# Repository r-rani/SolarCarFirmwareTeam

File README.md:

# SolarCarFirmwareTeam
Firmware and CANBUS implementation across the Solar Car

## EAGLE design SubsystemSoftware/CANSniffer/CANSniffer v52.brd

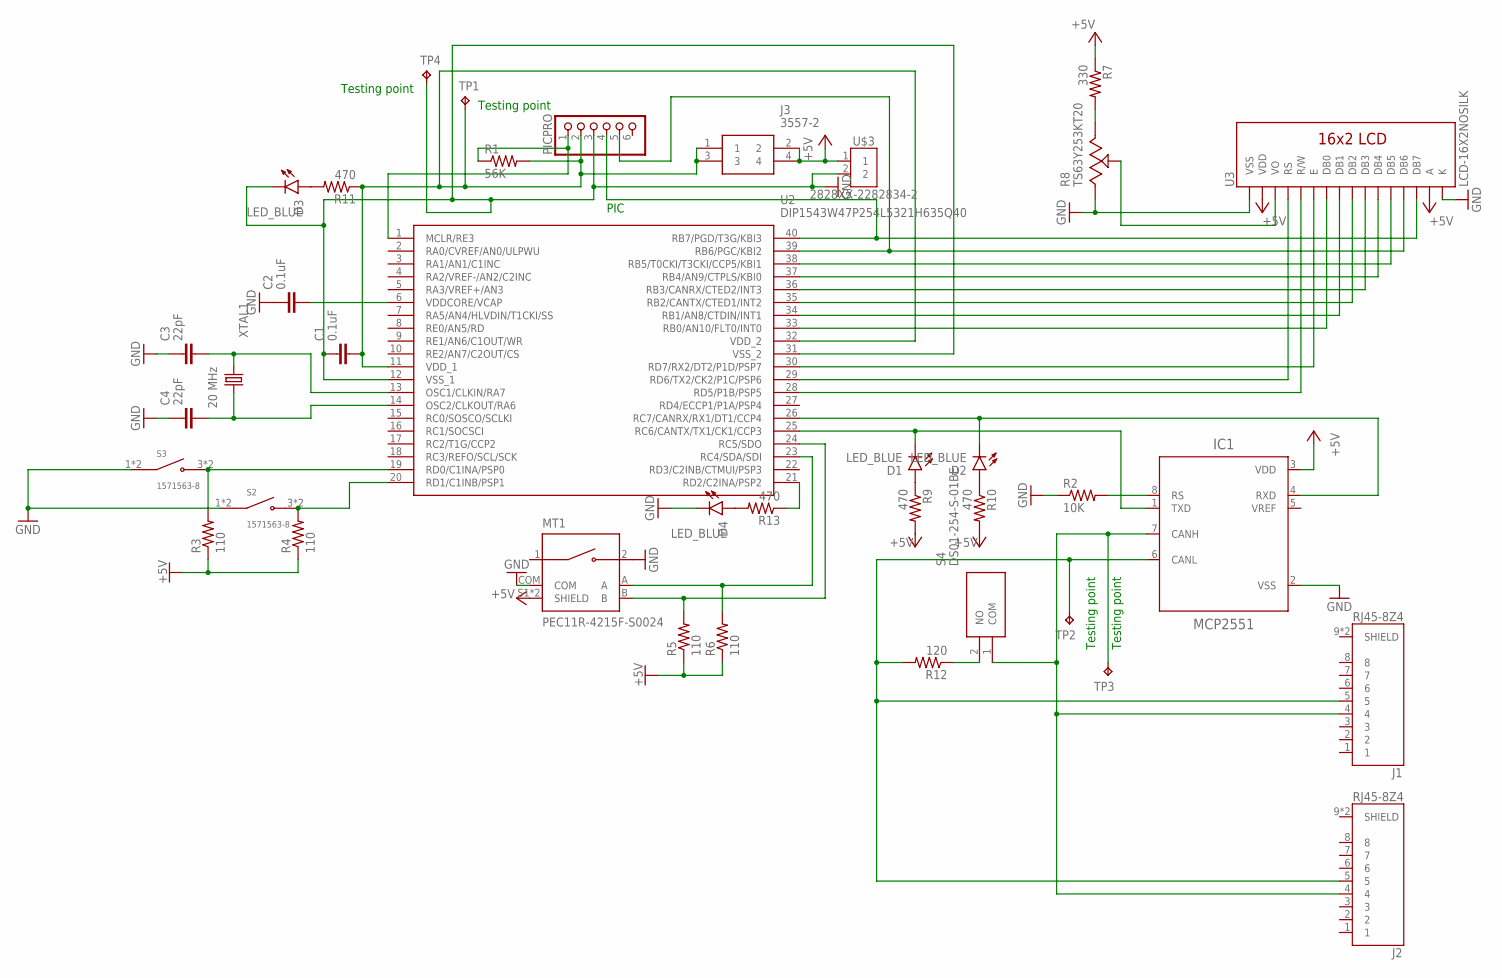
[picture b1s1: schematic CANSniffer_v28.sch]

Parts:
C1, C2: 0.1uF; CAPC3216X135
C3, C4: 22pF; CAPC3216X135
D1, D2, D3, D4: LED_BLUE; LEDC1005X25N_FLAT-B
IC1: MCP2551; DIP1092W55P254L949H533Q8B
J1, J2: RJ45-8Z4; TE_RJ45-8Z4
J3: 3557-2
MT1: PEC11R-4215F-S0024; XDCR_PEC11R-4215F-S0024
PICPRO: PINHD-1X6; 1X06
R1: 56K; R0603
R2: 10K; R0603
R3, R4, R5, R6: 110; R0603
R7: 330; R0603
R8: TS63Y253KT20; TRIM_TS63Y253KT20
R9, R10, R11, R13: 470; R0603
R12: 120; R0603
S2, S3: 1571563-8; SW_1571563-8
S4: DS01-254-S-01BE; DS01254S01BE
TP1, TP2, TP3, TP4: TPTP16R; TP16R
U2: DIP1543W47P254L5321H635Q40
U3: LCD-16X2NOSILK; LCD-16X2_NOSILK
U$3: 2828XX-2282834-2; TERMBLK_254-2N
XTAL1: 20 MHz; XTALRR488W45L1150T500H350B

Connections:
+5V: IC1.3 (VDD), J3.2, J3.4, MT1.S1 (SHIELD), MT1.S2 (SHIELD), R3.1, R4.1, R5.1, R6.1, R7.1, R9.2, R10.2, U3.2 (VDD), U3.15 (A), U$3.1
GND: C1.1, C2.1, C3.1, C4.1, D3.C, D4.C, IC1.2 (VSS), MT1.2, MT1.COM, PICPRO.3, R2.1, S2.1 (COM), S2.2 (COM), S3.1 (COM), S3.2 (COM), TP4.TP, U2.12 (VSS_1), U2.31 (VSS_2), U3.16 (K), U$3.2
unnamed: PICPRO.1, R1.1, U2.1 (MCLR/RE3)
unnamed: U2.33 (RB0/AN10/FLT0/INT0), U3.7 (DB0)
unnamed: IC1.8 (RS), R2.2
unnamed: D1.C, IC1.1 (TXD), U2.25 (RC6/CANTX/TX1/CK1/CCP3)
unnamed: PICPRO.4, U2.40 (RB7/PGD/T3G/KBI3), U3.14 (DB7)
unnamed: PICPRO.5, U2.39 (RB6/PGC/KBI2), U3.13 (DB6)
unnamed: U2.34 (RB1/AN8/CTDIN/INT1), U3.8 (DB1)
unnamed: U2.35 (RB2/CANTX/CTED1/INT2), U3.9 (DB2)
unnamed: D2.C, IC1.4 (RXD), U2.26 (RC7/CANRX/RX1/DT1/CCP4)
unnamed: C3.2, U2.13 (OSC1/CLKIN/RA7), XTAL1.1
unnamed: C4.2, U2.14 (OSC2/CLKOUT/RA6), XTAL1.2
unnamed: IC1.6 (CANL), J1.5, J2.5, R12.2, TP2.TP
unnamed: IC1.7 (CANH), J1.4, J2.4, S4.1 (COM), TP3.TP
unnamed: U2.36 (RB3/CANRX/CTED2/INT3), U3.10 (DB3)
unnamed: U2.37 (RB4/AN9/CTPLS/KBI0), U3.11 (DB4)
unnamed: U2.38 (RB5/T0CKI/T3CKI/CCP5/KBI1), U3.12 (DB5)
unnamed: U2.28 (RD5/P1B/PSP5), U3.5 (R/W)
unnamed: U2.29 (RD6/TX2/CK2/P1C/PSP6), U3.4 (RS)
unnamed: U2.30 (RD7/RX2/DT2/P1D/PSP7), U3.6 (E)
unnamed: D2.A, R10.1
unnamed: R7.2, R8.3 (C)
unnamed: R3.2, S3.3 (NO), S3.4 (NO), U2.19 (RD0/C1INA/PSP0)
unnamed: R4.2, S2.3 (NO), S2.4 (NO), U2.20 (RD1/C1INB/PSP1)
unnamed: C2.2, U2.6 (VDDCORE/VCAP)
unnamed: MT1.A, R6.2, U2.23 (RC4/SDA/SDI)
unnamed: MT1.B, R5.2, U2.24 (RC5/SDO)
unnamed: R8.2 (B), U3.3 (VO)
unnamed: D1.A, R9.1
unnamed: R12.1, S4.2 (NO)
unnamed: C1.2, J3.1, J3.3, PICPRO.2, R1.2, R11.1, TP1.TP, U2.11 (VDD_1), U2.32 (VDD_2)
unnamed: R8.1 (A), U3.1 (VSS)
unnamed: D3.A, R11.2
unnamed: D4.A, R13.2
unnamed: R13.1, U2.21 (RD2/C2INA/PSP2)

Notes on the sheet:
PIC
Testing point

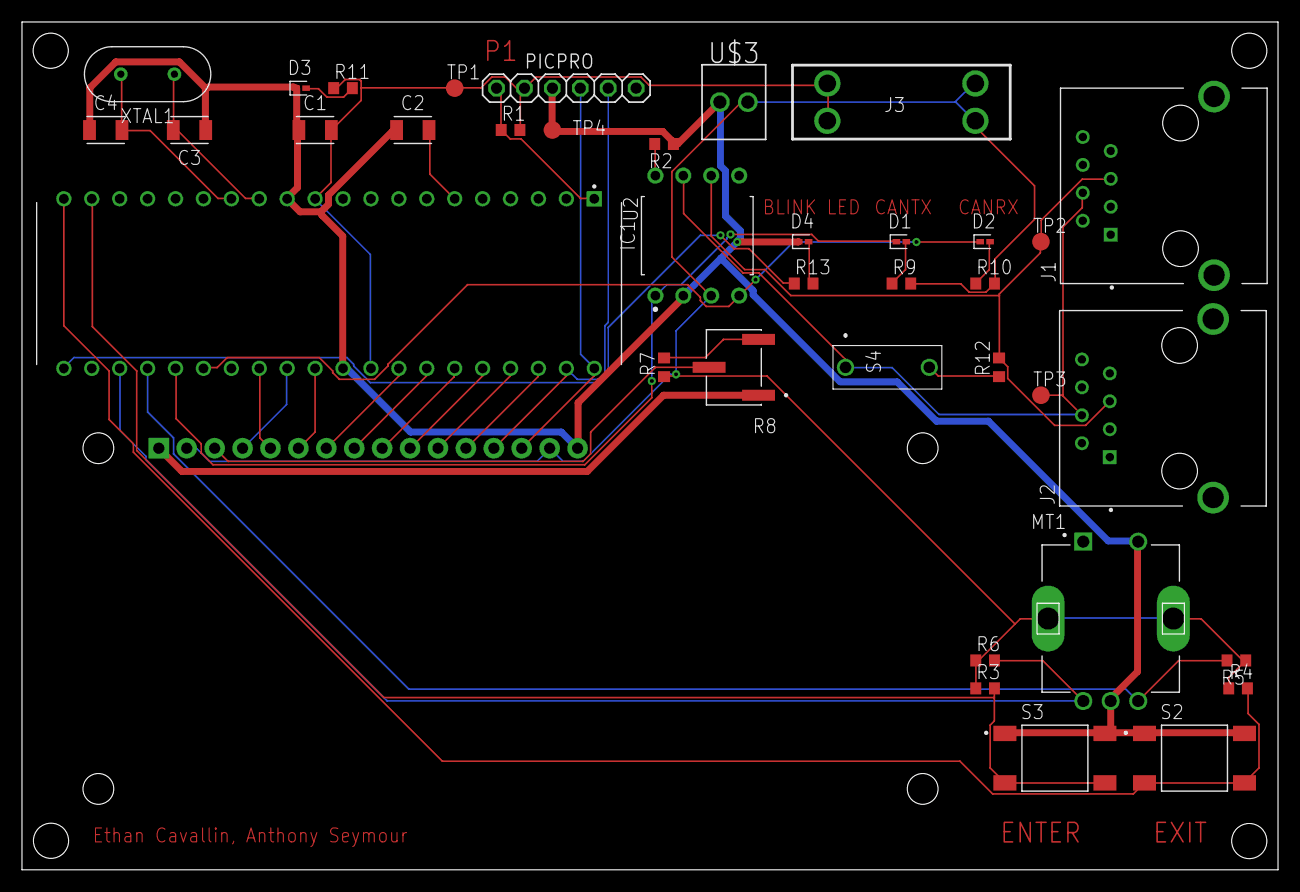
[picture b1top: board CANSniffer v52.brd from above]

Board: 2 copper layers, 114.3 x 77.1 mm, 38 parts (0 on the bottom side), 36 nets.

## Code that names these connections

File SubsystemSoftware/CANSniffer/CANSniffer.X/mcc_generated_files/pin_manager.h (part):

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// get/set IO_RB0 aliases
#define IO_RB0_TRIS                 TRISBbits.TRISB0
#define IO_RB0_LAT                  LATBbits.LATB0
#define IO_RB0_PORT                 PORTBbits.RB0
#define IO_RB0_WPU                  WPUBbits.WPUB0
#define IO_RB0_ANS                  ANCON1bits.ANSEL10
#define IO_RB0_SetHigh()            do { LATBbits.LATB0 = 1; } while(0)
#define IO_RB0_SetLow()             do { LATBbits.LATB0 = 0; } while(0)
#define IO_RB0_Toggle()             do { LATBbits.LATB0 = ~LATBbits.LATB0; } while(0)
#define IO_RB0_GetValue()           PORTBbits.RB0
#define IO_RB0_SetDigitalInput()    do { TRISBbits.TRISB0 = 1; } while(0)
#define IO_RB0_SetDigitalOutput()   do { TRISBbits.TRISB0 = 0; } while(0)
#define IO_RB0_SetPullup()          do { WPUBbits.WPUB0 = 1; } while(0)
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// get/set IO_RB1 aliases
#define IO_RB1_TRIS                 TRISBbits.TRISB1
#define IO_RB1_LAT                  LATBbits.LATB1
#define IO_RB1_PORT                 PORTBbits.RB1
#define IO_RB1_WPU                  WPUBbits.WPUB1
#define IO_RB1_ANS                  ANCON1bits.ANSEL8
#define IO_RB1_SetHigh()            do { LATBbits.LATB1 = 1; } while(0)
#define IO_RB1_SetLow()             do { LATBbits.LATB1 = 0; } while(0)
#define IO_RB1_Toggle()             do { LATBbits.LATB1 = ~LATBbits.LATB1; } while(0)
#define IO_RB1_GetValue()           PORTBbits.RB1
#define IO_RB1_SetDigitalInput()    do { TRISBbits.TRISB1 = 1; } while(0)
#define IO_RB1_SetDigitalOutput()   do { TRISBbits.TRISB1 = 0; } while(0)
#define IO_RB1_SetPullup()          do { WPUBbits.WPUB1 = 1; } while(0)
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// get/set IO_RB2 aliases
#define IO_RB2_TRIS                 TRISBbits.TRISB2
#define IO_RB2_LAT                  LATBbits.LATB2
#define IO_RB2_PORT                 PORTBbits.RB2
#define IO_RB2_WPU                  WPUBbits.WPUB2
#define IO_RB2_SetHigh()            do { LATBbits.LATB2 = 1; } while(0)
#define IO_RB2_SetLow()             do { LATBbits.LATB2 = 0; } while(0)
#define IO_RB2_Toggle()             do { LATBbits.LATB2 = ~LATBbits.LATB2; } while(0)
#define IO_RB2_GetValue()           PORTBbits.RB2
#define IO_RB2_SetDigitalInput()    do { TRISBbits.TRISB2 = 1; } while(0)
#define IO_RB2_SetDigitalOutput()   do { TRISBbits.TRISB2 = 0; } while(0)
#define IO_RB2_SetPullup()          do { WPUBbits.WPUB2 = 1; } while(0)
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// get/set IO_RB3 aliases
#define IO_RB3_TRIS                 TRISBbits.TRISB3
#define IO_RB3_LAT                  LATBbits.LATB3
#define IO_RB3_PORT                 PORTBbits.RB3
#define IO_RB3_WPU                  WPUBbits.WPUB3
#define IO_RB3_SetHigh()            do { LATBbits.LATB3 = 1; } while(0)
#define IO_RB3_SetLow()             do { LATBbits.LATB3 = 0; } while(0)
#define IO_RB3_Toggle()             do { LATBbits.LATB3 = ~LATBbits.LATB3; } while(0)
#define IO_RB3_GetValue()           PORTBbits.RB3
#define IO_RB3_SetDigitalInput()    do { TRISBbits.TRISB3 = 1; } while(0)
#define IO_RB3_SetDigitalOutput()   do { TRISBbits.TRISB3 = 0; } while(0)
#define IO_RB3_SetPullup()          do { WPUBbits.WPUB3 = 1; } while(0)
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// get/set IO_RB4 aliases
#define IO_RB4_TRIS                 TRISBbits.TRISB4
#define IO_RB4_LAT                  LATBbits.LATB4
#define IO_RB4_PORT                 PORTBbits.RB4
#define IO_RB4_WPU                  WPUBbits.WPUB4
#define IO_RB4_ANS                  ANCON1bits.ANSEL9
#define IO_RB4_SetHigh()            do { LATBbits.LATB4 = 1; } while(0)
#define IO_RB4_SetLow()             do { LATBbits.LATB4 = 0; } while(0)
#define IO_RB4_Toggle()             do { LATBbits.LATB4 = ~LATBbits.LATB4; } while(0)
#define IO_RB4_GetValue()           PORTBbits.RB4
#define IO_RB4_SetDigitalInput()    do { TRISBbits.TRISB4 = 1; } while(0)
#define IO_RB4_SetDigitalOutput()   do { TRISBbits.TRISB4 = 0; } while(0)
#define IO_RB4_SetPullup()          do { WPUBbits.WPUB4 = 1; } while(0)
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// get/set IO_RB5 aliases
#define IO_RB5_TRIS                 TRISBbits.TRISB5
#define IO_RB5_LAT                  LATBbits.LATB5
#define IO_RB5_PORT                 PORTBbits.RB5
#define IO_RB5_WPU                  WPUBbits.WPUB5
#define IO_RB5_SetHigh()            do { LATBbits.LATB5 = 1; } while(0)
#define IO_RB5_SetLow()             do { LATBbits.LATB5 = 0; } while(0)
#define IO_RB5_Toggle()             do { LATBbits.LATB5 = ~LATBbits.LATB5; } while(0)
#define IO_RB5_GetValue()           PORTBbits.RB5
#define IO_RB5_SetDigitalInput()    do { TRISBbits.TRISB5 = 1; } while(0)
#define IO_RB5_SetDigitalOutput()   do { TRISBbits.TRISB5 = 0; } while(0)
#define IO_RB5_SetPullup()          do { WPUBbits.WPUB5 = 1; } while(0)
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// get/set IO_RB6 aliases
#define IO_RB6_TRIS                 TRISBbits.TRISB6
#define IO_RB6_LAT                  LATBbits.LATB6
#define IO_RB6_PORT                 PORTBbits.RB6
#define IO_RB6_WPU                  WPUBbits.WPUB6
#define IO_RB6_SetHigh()            do { LATBbits.LATB6 = 1; } while(0)
#define IO_RB6_SetLow()             do { LATBbits.LATB6 = 0; } while(0)
#define IO_RB6_Toggle()             do { LATBbits.LATB6 = ~LATBbits.LATB6; } while(0)
#define IO_RB6_GetValue()           PORTBbits.RB6
#define IO_RB6_SetDigitalInput()    do { TRISBbits.TRISB6 = 1; } while(0)
#define IO_RB6_SetDigitalOutput()   do { TRISBbits.TRISB6 = 0; } while(0)
#define IO_RB6_SetPullup()          do { WPUBbits.WPUB6 = 1; } while(0)
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// get/set IO_RB7 aliases
#define IO_RB7_TRIS                 TRISBbits.TRISB7
#define IO_RB7_LAT                  LATBbits.LATB7
#define IO_RB7_PORT                 PORTBbits.RB7
#define IO_RB7_WPU                  WPUBbits.WPUB7
#define IO_RB7_SetHigh()            do { LATBbits.LATB7 = 1; } while(0)
#define IO_RB7_SetLow()             do { LATBbits.LATB7 = 0; } while(0)
#define IO_RB7_Toggle()             do { LATBbits.LATB7 = ~LATBbits.LATB7; } while(0)
#define IO_RB7_GetValue()           PORTBbits.RB7
#define IO_RB7_SetDigitalInput()    do { TRISBbits.TRISB7 = 1; } while(0)
#define IO_RB7_SetDigitalOutput()   do { TRISBbits.TRISB7 = 0; } while(0)
#define IO_RB7_SetPullup()          do { WPUBbits.WPUB7 = 1; } while(0)
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// get/set IO_RC4 aliases
#define IO_RC4_TRIS                 TRISCbits.TRISC4
#define IO_RC4_LAT                  LATCbits.LATC4
#define IO_RC4_PORT                 PORTCbits.RC4
#define IO_RC4_SetHigh()            do { LATCbits.LATC4 = 1; } while(0)
#define IO_RC4_SetLow()             do { LATCbits.LATC4 = 0; } while(0)
#define IO_RC4_Toggle()             do { LATCbits.LATC4 = ~LATCbits.LATC4; } while(0)
#define IO_RC4_GetValue()           PORTCbits.RC4
#define IO_RC4_SetDigitalInput()    do { TRISCbits.TRISC4 = 1; } while(0)
#define IO_RC4_SetDigitalOutput()   do { TRISCbits.TRISC4 = 0; } while(0)

// get/set IO_RC5 aliases
#define IO_RC5_TRIS                 TRISCbits.TRISC5
#define IO_RC5_LAT                  LATCbits.LATC5
#define IO_RC5_PORT                 PORTCbits.RC5
#define IO_RC5_SetHigh()            do { LATCbits.LATC5 = 1; } while(0)
#define IO_RC5_SetLow()             do { LATCbits.LATC5 = 0; } while(0)
#define IO_RC5_Toggle()             do { LATCbits.LATC5 = ~LATCbits.LATC5; } while(0)
#define IO_RC5_GetValue()           PORTCbits.RC5
#define IO_RC5_SetDigitalInput()    do { TRISCbits.TRISC5 = 1; } while(0)
#define IO_RC5_SetDigitalOutput()   do { TRISCbits.TRISC5 = 0; } while(0)

// get/set IO_RC6 aliases
#define IO_RC6_TRIS                 TRISCbits.TRISC6
#define IO_RC6_LAT                  LATCbits.LATC6
#define IO_RC6_PORT                 PORTCbits.RC6
#define IO_RC6_SetHigh()            do { LATCbits.LATC6 = 1; } while(0)
#define IO_RC6_SetLow()             do { LATCbits.LATC6 = 0; } while(0)
#define IO_RC6_Toggle()             do { LATCbits.LATC6 = ~LATCbits.LATC6; } while(0)
#define IO_RC6_GetValue()           PORTCbits.RC6
#define IO_RC6_SetDigitalInput()    do { TRISCbits.TRISC6 = 1; } while(0)
#define IO_RC6_SetDigitalOutput()   do { TRISCbits.TRISC6 = 0; } while(0)

// get/set IO_RC7 aliases
#define IO_RC7_TRIS                 TRISCbits.TRISC7
#define IO_RC7_LAT                  LATCbits.LATC7
#define IO_RC7_PORT                 PORTCbits.RC7
#define IO_RC7_SetHigh()            do { LATCbits.LATC7 = 1; } while(0)
#define IO_RC7_SetLow()             do { LATCbits.LATC7 = 0; } while(0)
#define IO_RC7_Toggle()             do { LATCbits.LATC7 = ~LATCbits.LATC7; } while(0)
#define IO_RC7_GetValue()           PORTCbits.RC7
#define IO_RC7_SetDigitalInput()    do { TRISCbits.TRISC7 = 1; } while(0)
#define IO_RC7_SetDigitalOutput()   do { TRISCbits.TRISC7 = 0; } while(0)

// get/set IO_RD0 aliases
#define IO_RD0_TRIS                 TRISDbits.TRISD0
#define IO_RD0_LAT                  LATDbits.LATD0
#define IO_RD0_PORT                 PORTDbits.RD0
#define IO_RD0_ANS                  ANCON1bits.ANSEL11
#define IO_RD0_SetHigh()            do { LATDbits.LATD0 = 1; } while(0)
#define IO_RD0_SetLow()             do { LATDbits.LATD0 = 0; } while(0)
#define IO_RD0_Toggle()             do { LATDbits.LATD0 = ~LATDbits.LATD0; } while(0)
#define IO_RD0_GetValue()           PORTDbits.RD0
#define IO_RD0_SetDigitalInput()    do { TRISDbits.TRISD0 = 1; } while(0)
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
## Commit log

2023-03-04 Code for LV
2023-03-04 changed folder name
2023-03-04 BMS Datasheet
2023-03-05 Added DDISP
2023-03-05 Added CANSniffer
2023-03-05 Uploaded CANSniffer Schematics
2023-03-12 test commit to master
2023-03-12 Added functionality to LCD
2023-03-26 Made changes to DDISP firmware
2023-04-02 Motor Controller Can IDs Header File
2023-05-13 added canbus test code
2023-07-09 PMS Updated Code Rev1
2023-07-17 PMS Updated Code - Compilation Working
2023-07-17 PMS Updated Code - Building Successfully (ignore previous commit pls)
2023-07-20 added code for functional testing
2023-07-30 committed DDISP
2023-07-30 Added functionality to DDISP
2023-07-30 Added final LV
2023-08-11 Made changes and added ADC. More changes to be made and are specified in code
2023-08-11 switched pin 9 to GPIO from ADC
2023-08-12 CHanged the ADC function
2023-08-12 edited PMS
2023-08-12 changed CANBUS variable name
2023-08-12 made some edits
2023-08-28 Worked on PMS
2023-09-13 started new latching project, push pending clarification on pinout
2023-09-13 Latching MCC config finished, interrupts enabled on pins B0-3, CAN over RC6/7, relay enable over pin RD1
2023-09-14 Added global variables and shutdown function
2023-09-19 Added function for shutdown-normal
2023-09-19 added CAN poll- pending ID type
2023-09-19 Changed if statement so that RB3 reads for 1
2023-09-19 Removed comments to enable global interrupts
2023-09-19 added latchOn to ext_int
2023-09-19 Completed PMS V2 start up sequence
2023-09-20 added can tx notes
2023-09-20 completed startup for latch circuit
2023-09-20 added new can message variables
2023-09-20 amended canbus
2023-09-20 added interrupt trigger for start and shut down
2023-09-21 added shutdown msg, should be ready for testing
2023-09-21 Moved pin ISR to main.c, added some experimental CAN interrupt functionality- ready for testing
2023-09-21 tweaks to make it build properly
2023-09-21 PMS V2 Firmware complete (NOT TESTED)
2023-09-21 more testing, moved fully to polling
2023-09-27 PMS Firmware almost complete, cloned Latching
2023-09-27 Latching circuit complete w/o canbus
2023-10-03 local save
2023-10-03 Updated shutdown condition so that shutdown occurs once LatchOn flag is true
2023-10-05 debug changes to PMS
2023-10-05 Debugging changes to PMS
2023-10-25 Testing ADC, works by itself but not in PMS
2023-10-31 removed my stats formula sheet
2023-11-08 added functionality for integration to DDISP
2023-11-08 updated CAN IDs
2023-11-29 Updated main.c, PMS works
2023-11-29 why?
2023-11-30 no change
2023-11-30 break added to func w shutdown
2023-11-30 integration progress on DDISP
2023-11-30 changed canbus codes
2023-11-30 changed BPS FAULT to 0x12, changed OK to 0x9
2023-12-01 added variables, added header file for the canbus sending function, added delay for the OK function
2023-12-06 work on DDISP integration
2023-12-06 Working integration of DDISP, LV and PMS. TODO: implement a starting delay of 1000ms on PMS, implement a BPS fault OFF CAN message on LV for canbus msg ok
2024-01-16 pushed changes
2024-01-16 Added BPS fault off CAN message for canbus ok
2024-01-28 New PMS version launched
2024-01-30 Added start delay
2024-02-06 Added 700ms delay to BPS fault
2024-02-13 added SOC and temp variables to DDISP

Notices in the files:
SubsystemSoftware/CANSniffer/CANSniffer.X/mcc_generated_files/pin_manager.h:
(c) 2018 Microchip Technology Inc. and its subsidiaries.
